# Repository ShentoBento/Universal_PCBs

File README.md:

# Universal PCBs
note: this was a draft written by AI, its got a ton of errors and is pending manual changes
**Open-source, QMK/VIA-compatible keyboard PCBs designed to fit as many cases as possible.**

Most custom keyboard cases are designed around one specific PCB. The boards in this repo work the other way around. Each one is built to drop into as many cases of its form factor as possible, by supporting a wide range of layouts and matching the connector and mounting positions that different cases expect.

---

## Boards

| Board | Form factor | Type | Status | Firmware |
|---|---|---|---|---|
| [**Uni60 Solder**](Uni60/UNI60_Solder) | 60% | Solder | Completed 50 unit GB, Sep 2026 | [Uni60/Solder](https://github.com/ShentoBento/Universal_PCBs_Firmware/tree/main/Uni60/Solder) |
| [**Uni60 Hotswap**](Uni60/UNI60_Hotswap) | 60% | Hotswap | In development | — |

Each board's folder has its own README with full specs, layout diagrams and ordering files.

---

## What "universal" means here

**Layouts.** Each board supports the common layout variations for its size. The Uni60 covers ANSI and ISO, split backspace, split left and right shift, stepped caps, and five bottom rows: 6.25u, 7u, 10u, 2.25u/1.25u/2.75u split, and 3u/1u/3u split.

**Connectors.** Enthusiast cases route the USB daughterboard cable through a channel, and that channel sits in a different place in nearly every case. A tall JST-SH connector anywhere else bottoms out on the case floor. So the Uni60 has **five daisy-chained JST-SH positions** that line up with common channel locations. Keep the one your case uses and clip or desolder the rest. There's also a **Molex Pico-EZmate** connector, which sits lower than the switch pins and fits any case.

**Outline and mounting.** The board outline is drawn to suit as many cases as possible. It includes tray-mount holes between keys, with the switch matrix routed around them.

---

## Shared specs

- **MCU:** STM32F072CBTx
- **Connectors:** JST-SH 4-pin (multiple positions) and Molex Pico-EZmate 4-pin
- **Firmware:** QMK with VIA and Vial support, in [Universal_PCBs_Firmware](https://github.com/ShentoBento/Universal_PCBs_Firmware)
- **Design tool:** KiCad 10 or newer (earlier versions won't open the files)
- **Manufacturing:** fab and assembly files generated for JLCPCB

---

## Repository layout

```
Universal_PCBs/
├── Uni60/
│   ├── UNI60_Solder/              complete: KiCad project, production files, images
│   └── UNI60_Hotswap/             in development
└── shentobento_kicad_library/     shared symbols, footprints and 3D models
```

## Using these files

1. Clone or download the **whole repo**, not just one board's folder. Every board points at the shared `shentobento_kicad_library/` with relative paths, so the projects open on any machine with no library setup.
2. Open the board's `.kicad_pro` file in KiCad 10 or newer.
3. To order boards, use the files in that board's `production/` folder (gerbers, BOM, positions). If you change the design, regenerate them with the JLCPCB Fabrication Toolkit plugin.

## Related

- [Universal_PCBs_Firmware](https://github.com/ShentoBento/Universal_PCBs_Firmware): QMK firmware for these boards
- [Velvet-Pro-Solder-PCB](https://github.com/ShentoBento/Velvet-Pro-Solder-PCB): the board whose matrix and MCU design the Uni60 builds on

## Credits and licenses

Keyboard footprints and symbols are derived from [marbastlib](https://github.com/ebastler/marbastlib) by ebastler, licensed under CERN-OHL-P v2. See `shentobento_kicad_library/LICENSE-marbastlib.txt`; modifications are logged in `shentobento_kicad_library/NOTICE.md`. Generic footprints come from the KiCad standard libraries.

---

Designed by **Andrew Shentu** ([@ShentoBento](https://github.com/ShentoBento)) · [LinkedIn](https://www.linkedin.com/in/andrewshentu)

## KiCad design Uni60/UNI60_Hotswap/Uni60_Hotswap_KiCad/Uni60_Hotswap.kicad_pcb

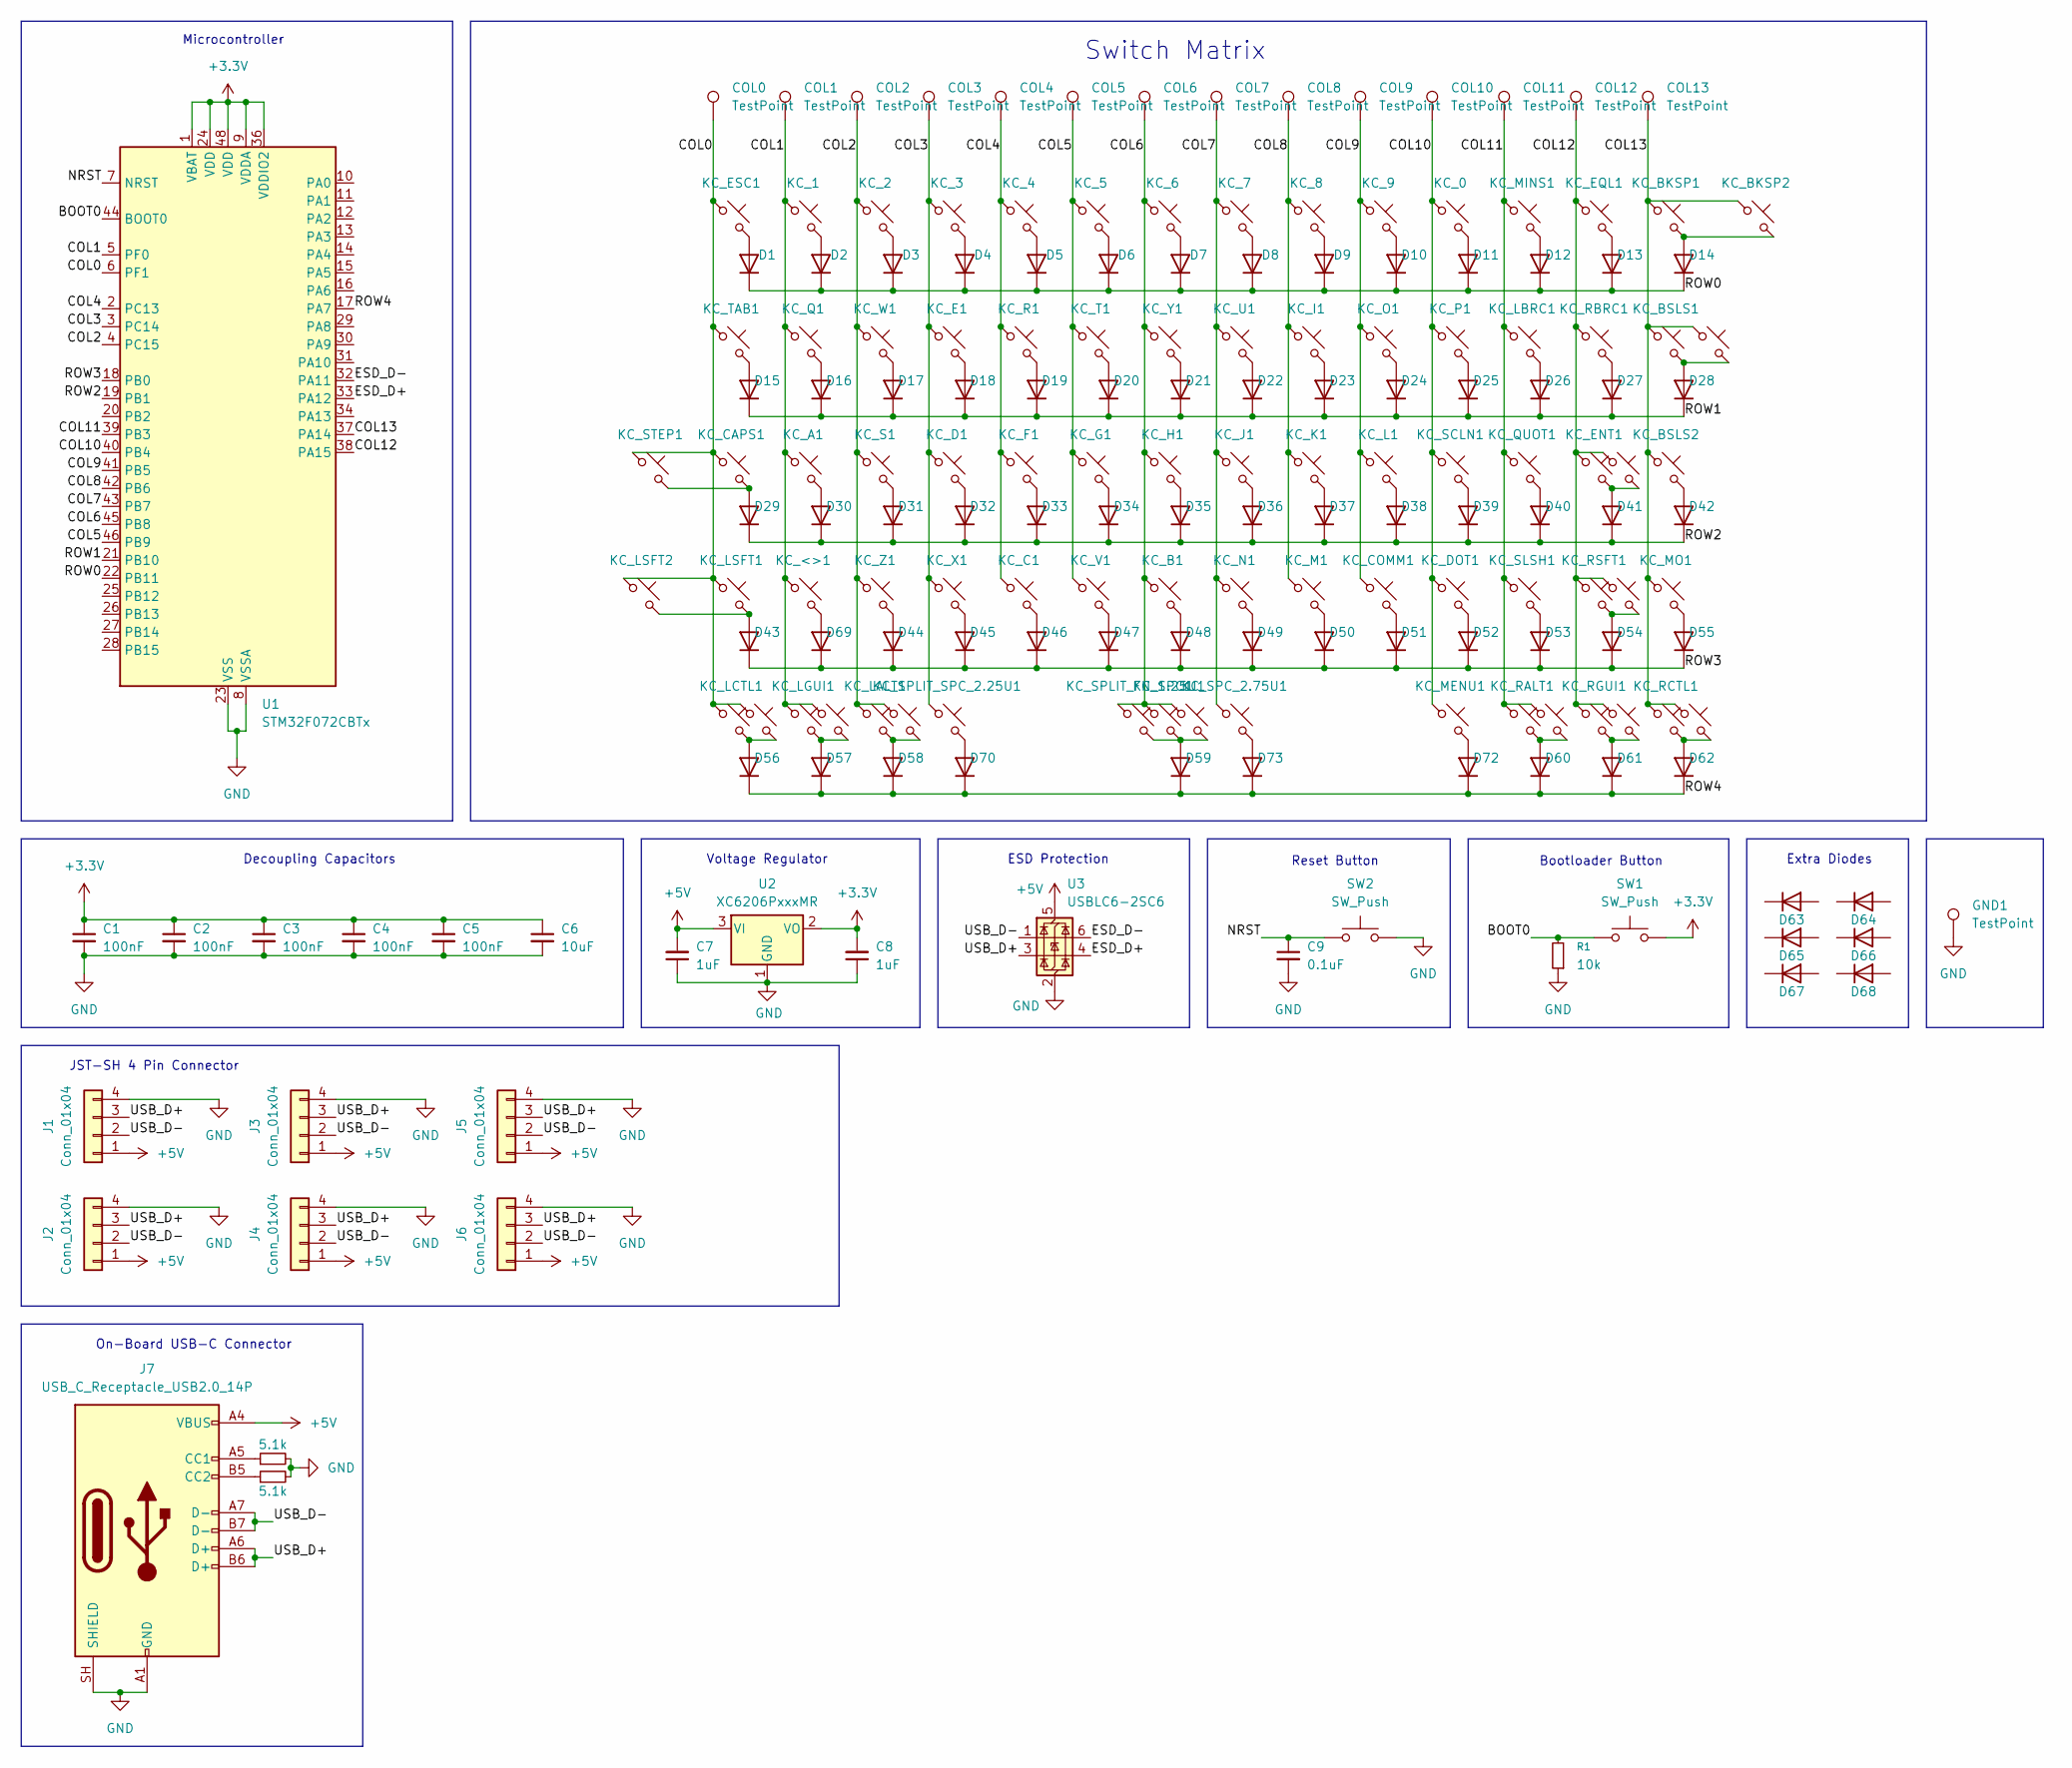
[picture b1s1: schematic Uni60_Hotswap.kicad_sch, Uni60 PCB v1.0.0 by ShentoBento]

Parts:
C1, C2, C3, C4, C5: 100nF; C_0201_0603Metric
C6: 10uF; C_0805_2012Metric
C7, C8: 1uF; C_0201_0603Metric
C9: 0.1uF; C_0201_0603Metric
COL0, COL1, COL2, COL3, COL4, COL5, COL6, COL7, COL8, COL9, COL10, COL11, COL12, COL13: TestPoint; TestPoint_Pad_1.5x1.5mm
D1, D2, D3, D4, D5, D6, D7, D8, D9, D10, D11, D12, D13, D14, D15, D16, D17, D18, D19, D20, D21, D22, D23, D24, D25, D26, D27, D28, D29, D30, D31, D32, D33, D34, D35, D36, D37, D38, D39, D40, D41, D42, D43, D44, D45, D46, D47, D48, D49, D50, D51, D52, D53, D54, D55, D56, D57, D58, D59, D60, D61, D62, D63, D64, D65, D66, D67, D68, D69, D70, D72, D73: 1N4148; D_SOD-323
GND1: TestPoint; TestPoint_Bridge_Pitch2.0mm_Drill0.7mm
J1, J2, J3, J4, J5: Conn_01x04; JST_SH_1x04
J6: Conn_01x04; Molex_Pico-EZmate_78171-0004_1x04-1MP_P1.20mm_Vertical
J7: USB_C_Receptacle_USB2.0_14P; USB_C_Receptacle_GCT_USB4105-xx-A_16P_TopMnt_Horizontal
KC_0, KC_1, KC_2, KC_3, KC_4, KC_5, KC_6, KC_7, KC_8, KC_9: MX_SW_solder; SW_MX_HS_KAILH_1u
KC_<>1: MX_SW_solder; SW_MX_HS_KAILH_1u
KC_A1: MX_SW_solder; SW_MX_HS_KAILH_1u
KC_B1: MX_SW_solder; SW_MX_HS_KAILH_1u
KC_BKSP1, KC_BKSP2: MX_SW_solder; SW_MX_HS_KAILH_1u
KC_BSLS1: MX_SW_solder; SW_MX_HS_KAILH_1.5u
KC_BSLS2: MX_SW_solder; SW_MX_HS_KAILH_1u
KC_BSLS_ISO1: MX_SW_solder; SW_MX_HS_KAILH_1u
KC_C1: MX_SW_solder; SW_MX_HS_KAILH_1u
KC_CAPS1: MX_SW_solder; SW_MX_HS_KAILH_1.75u
KC_COMM1: MX_SW_solder; SW_MX_HS_KAILH_1u
KC_D1: MX_SW_solder; SW_MX_HS_KAILH_1u
KC_DOT1: MX_SW_solder; SW_MX_HS_KAILH_1u
KC_E1: MX_SW_solder; SW_MX_HS_KAILH_1u
KC_ENT1: MX_SW_solder; SW_MX_HS_KAILH_1u
KC_ENT_ISO1: MX_SW_solder; SW_MX_HS_KAILH_1u
KC_EQL1: MX_SW_solder; SW_MX_HS_KAILH_1u
KC_ESC1: MX_SW_solder; SW_MX_HS_KAILH_1u
KC_F1: MX_SW_solder; SW_MX_HS_KAILH_1u
KC_G1: MX_SW_solder; SW_MX_HS_KAILH_1u
KC_H1: MX_SW_solder; SW_MX_HS_KAILH_1u
KC_I1: MX_SW_solder; SW_MX_HS_KAILH_1u
KC_J1: MX_SW_solder; SW_MX_HS_KAILH_1u
KC_K1: MX_SW_solder; SW_MX_HS_KAILH_1u
KC_L1: MX_SW_solder; SW_MX_HS_KAILH_1u
KC_LALT1: MX_SW_solder; SW_MX_HS_KAILH_1.5u
KC_LALT_1.25U1: MX_SW_solder; SW_MX_HS_KAILH_1.25u
KC_LBRC1: MX_SW_solder; SW_MX_HS_KAILH_1u
KC_LCTL1: MX_SW_solder; SW_MX_HS_KAILH_1.5u
KC_LCTL_1.25U1: MX_SW_solder; SW_MX_HS_KAILH_1.25u
KC_LGUI1: MX_SW_solder; SW_MX_HS_KAILH_1u
KC_LGUI_1.25U1: MX_SW_solder; SW_MX_HS_KAILH_1.25u
KC_LSFT1: MX_SW_solder; SW_MX_HS_KAILH_1u
KC_LSFT2: MX_SW_solder; SW_MX_HS_KAILH_1.25u
KC_M1: MX_SW_solder; SW_MX_HS_KAILH_1u
KC_MENU1: MX_SW_solder; SW_MX_HS_KAILH_1.25u
KC_MINS1: MX_SW_solder; SW_MX_HS_KAILH_1u
KC_MO1: MX_SW_solder; SW_MX_HS_KAILH_1u
KC_N1: MX_SW_solder; SW_MX_HS_KAILH_1u
KC_O1: MX_SW_solder; SW_MX_HS_KAILH_1u
KC_P1: MX_SW_solder; SW_MX_HS_KAILH_1u
KC_Q1: MX_SW_solder; SW_MX_HS_KAILH_1u
KC_QUOT1: MX_SW_solder; SW_MX_HS_KAILH_1u
KC_R1: MX_SW_solder; SW_MX_HS_KAILH_1u
KC_RALT1: MX_SW_solder; SW_MX_HS_KAILH_1.5u
KC_RALT_1.25U1: MX_SW_solder; SW_MX_HS_KAILH_1.25u
KC_RBRC1: MX_SW_solder; SW_MX_HS_KAILH_1u
KC_RCTL1: MX_SW_solder; SW_MX_HS_KAILH_1.5u
KC_RCTL_1.25U1: MX_SW_solder; SW_MX_HS_KAILH_1.25u
KC_RGUI1: MX_SW_solder; SW_MX_HS_KAILH_1u
KC_RGUI_1.25U1: MX_SW_solder; SW_MX_HS_KAILH_1.25u
KC_RSFT1: MX_SW_solder; SW_MX_HS_KAILH_1u
KC_RSFT_2.75u1: MX_SW_solder; SW_MX_HS_KAILH_1u
KC_S1: MX_SW_solder; SW_MX_HS_KAILH_1u
KC_SCLN1: MX_SW_solder; SW_MX_HS_KAILH_1u
KC_SLSH1: MX_SW_solder; SW_MX_HS_KAILH_1u
KC_SPC1: MX_SW_solder; SW_MX_HS_KAILH_1u
KC_SPC_2.75U1, KC_SPC_6.25U1: MX_SW_solder; SW_MX_HS_KAILH_1u
KC_SPLIT_FN_1.25U1: MX_SW_solder; SW_MX_HS_KAILH_1.25u
KC_SPLIT_SPC_2.25U1: MX_SW_solder; SW_MX_HS_KAILH_1u
KC_STEP1: MX_SW_solder; SW_MX_HS_KAILH_1.75u_STEPPED_1.25
KC_T1: MX_SW_solder; SW_MX_HS_KAILH_1u
KC_TAB1: MX_SW_solder; SW_MX_HS_KAILH_1.5u
KC_U1: MX_SW_solder; SW_MX_HS_KAILH_1u
KC_V1: MX_SW_solder; SW_MX_HS_KAILH_1u
KC_W1: MX_SW_solder; SW_MX_HS_KAILH_1u
KC_X1: MX_SW_solder; SW_MX_HS_KAILH_1u
KC_Y1: MX_SW_solder; SW_MX_HS_KAILH_1u
KC_Z1: MX_SW_solder; SW_MX_HS_KAILH_1u
R1: 10k; R_0201_0603Metric
R2, R3: 5.1k; R_0201_0603Metric
SW1, SW2: SW_Push; SW_Push_Reset_Bootloader
U1: STM32F072CBTx; MCU_STM32F072CBTx
U2: XC6206PxxxMR; SOT-23-3
U3: USBLC6-2SC6; SOT-23-6

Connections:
+3.3V: C1.1, C2.1, C3.1, C4.1, C5.1, C6.1, C8.2, SW1.2, U1.1 (VBAT), U1.9 (VDDA), U1.24 (VDD), U1.36 (VDDIO2), U1.48 (VDD), U2.2 (VO)
+5V: C7.2, J1.1, J2.1, J3.1, J4.1, J5.1, J6.1, J7.A4 (VBUS), J7.A9 (VBUS), J7.B4 (VBUS), J7.B9 (VBUS), U2.3 (VI), U3.5 (VBUS)
/BOOT0: R1.2, SW1.1, U1.44 (BOOT0)
/COL0: COL0.1 (1_1), KC_CAPS1.1, KC_ESC1.1, KC_LCTL1.1, KC_LCTL_1.25U1.1, KC_LSFT1.1, KC_LSFT2.1, KC_STEP1.1, KC_TAB1.1, U1.6 (PF1)
/COL1: COL1.1 (1_1), KC_1.1, KC_<>1.1, KC_A1.1, KC_LGUI1.1, KC_LGUI_1.25U1.1, KC_Q1.1, U1.5 (PF0)
/COL2: COL2.1 (1_1), KC_2.1, KC_LALT1.1, KC_LALT_1.25U1.1, KC_S1.1, KC_W1.1, KC_Z1.1, U1.4 (PC15)
/COL3: COL3.1 (1_1), KC_3.1, KC_D1.1, KC_E1.1, KC_SPLIT_SPC_2.25U1.1, KC_X1.1, U1.3 (PC14)
/COL4: COL4.1 (1_1), KC_4.1, KC_C1.1, KC_F1.1, KC_R1.1, U1.2 (PC13)
/COL5: COL5.1 (1_1), KC_5.1, KC_G1.1, KC_T1.1, KC_V1.1, U1.46 (PB9)
/COL6: COL6.1 (1_1), KC_6.1, KC_B1.1, KC_H1.1, KC_SPC1.1, KC_SPC_6.25U1.1, KC_SPLIT_FN_1.25U1.1, KC_Y1.1, U1.45 (PB8)
/COL7: COL7.1 (1_1), KC_7.1, KC_J1.1, KC_N1.1, KC_SPC_2.75U1.1, KC_U1.1, U1.43 (PB7)
/COL8: COL8.1 (1_1), KC_8.1, KC_I1.1, KC_K1.1, KC_M1.1, U1.42 (PB6)
/COL9: COL9.1 (1_1), KC_9.1, KC_COMM1.1, KC_L1.1, KC_O1.1, U1.41 (PB5)
/COL10: COL10.1 (1_1), KC_0.1, KC_DOT1.1, KC_MENU1.1, KC_P1.1, KC_SCLN1.1, U1.40 (PB4)
/COL11: COL11.1 (1_1), KC_LBRC1.1, KC_MINS1.1, KC_QUOT1.1, KC_RALT1.1, KC_RALT_1.25U1.1, KC_SLSH1.1, U1.39 (PB3)
/COL12: COL12.1 (1_1), KC_ENT1.1, KC_ENT_ISO1.1, KC_EQL1.1, KC_RBRC1.1, KC_RGUI1.1, KC_RGUI_1.25U1.1, KC_RSFT1.1, KC_RSFT_2.75u1.1, U1.38 (PA15)
/COL13: COL13.1 (1_1), KC_BKSP1.1, KC_BKSP2.1, KC_BSLS1.1, KC_BSLS2.1, KC_BSLS_ISO1.1, KC_MO1.1, KC_RCTL1.1, KC_RCTL_1.25U1.1, U1.37 (PA14)
/ESD_D+: U1.33 (PA12), U3.4 (I/O2)
/ESD_D-: U1.32 (PA11), U3.6 (I/O1)
/NRST: C9.1, SW2.1, U1.7 (NRST)
/ROW0: D1.1 (K), D2.1 (K), D3.1 (K), D4.1 (K), D5.1 (K), D6.1 (K), D7.1 (K), D8.1 (K), D9.1 (K), D10.1 (K), D11.1 (K), D12.1 (K), D13.1 (K), D14.1 (K), U1.22 (PB11)
/ROW1: D15.1 (K), D16.1 (K), D17.1 (K), D18.1 (K), D19.1 (K), D20.1 (K), D21.1 (K), D22.1 (K), D23.1 (K), D24.1 (K), D25.1 (K), D26.1 (K), D27.1 (K), D28.1 (K), U1.21 (PB10)
/ROW2: D29.1 (K), D30.1 (K), D31.1 (K), D32.1 (K), D33.1 (K), D34.1 (K), D35.1 (K), D36.1 (K), D37.1 (K), D38.1 (K), D39.1 (K), D40.1 (K), D41.1 (K), D42.1 (K), U1.19 (PB1)
/ROW3: D43.1 (K), D44.1 (K), D45.1 (K), D46.1 (K), D47.1 (K), D48.1 (K), D49.1 (K), D50.1 (K), D51.1 (K), D52.1 (K), D53.1 (K), D54.1 (K), D55.1 (K), D69.1 (K), U1.18 (PB0)
/ROW4: D56.1 (K), D57.1 (K), D58.1 (K), D59.1 (K), D60.1 (K), D61.1 (K), D62.1 (K), D70.1 (K), D72.1 (K), D73.1 (K), U1.17 (PA7)
/USB_D+: J1.3, J2.3, J3.3, J4.3, J5.3, J6.3, J7.A6 (D+), J7.B6 (D+), U3.3 (I/O2)
/USB_D-: J1.2, J2.2, J3.2, J4.2, J5.2, J6.2, J7.A7 (D-), J7.B7 (D-), U3.1 (I/O1)
GND: C1.2, C2.2, C3.2, C4.2, C5.2, C6.2, C7.1, C8.1, C9.2, GND1.1 (1_1), J1.4, J2.4, J3.4, J4.4, J5.4, J6.4, J7.A1 (GND), J7.A12 (GND), J7.B1 (GND), J7.B12 (GND), J7.SH (SHIELD), R1.1, R2.2, R3.2, SW2.2, U1.8 (VSSA), U1.23 (VSS), U1.35 (VSS), U1.47 (VSS), U2.1 (GND), U3.2 (GND)
unnamed: D1.2 (A), KC_ESC1.2
unnamed: D2.2 (A), KC_1.2
unnamed: D3.2 (A), KC_2.2
unnamed: D4.2 (A), KC_3.2
unnamed: D5.2 (A), KC_4.2
unnamed: D6.2 (A), KC_5.2
unnamed: D7.2 (A), KC_6.2
unnamed: D8.2 (A), KC_7.2
unnamed: D9.2 (A), KC_8.2
unnamed: D10.2 (A), KC_9.2
unnamed: D11.2 (A), KC_0.2
unnamed: D12.2 (A), KC_MINS1.2
unnamed: D13.2 (A), KC_EQL1.2
unnamed: D14.2 (A), KC_BKSP1.2, KC_BKSP2.2
unnamed: D15.2 (A), KC_TAB1.2
unnamed: D16.2 (A), KC_Q1.2
unnamed: D17.2 (A), KC_W1.2
unnamed: D18.2 (A), KC_E1.2
unnamed: D19.2 (A), KC_R1.2
unnamed: D20.2 (A), KC_T1.2
unnamed: D21.2 (A), KC_Y1.2
unnamed: D22.2 (A), KC_U1.2
unnamed: D23.2 (A), KC_I1.2
unnamed: D24.2 (A), KC_O1.2
unnamed: D25.2 (A), KC_P1.2
unnamed: D26.2 (A), KC_LBRC1.2
unnamed: D27.2 (A), KC_RBRC1.2
unnamed: D28.2 (A), KC_BSLS1.2, KC_BSLS_ISO1.2
unnamed: D29.2 (A), KC_CAPS1.2, KC_STEP1.2
unnamed: D30.2 (A), KC_A1.2
unnamed: D31.2 (A), KC_S1.2
unnamed: D32.2 (A), KC_D1.2
unnamed: D33.2 (A), KC_F1.2
unnamed: D34.2 (A), KC_G1.2
unnamed: D35.2 (A), KC_H1.2
unnamed: D36.2 (A), KC_J1.2
unnamed: D37.2 (A), KC_K1.2
unnamed: D38.2 (A), KC_L1.2
unnamed: D39.2 (A), KC_SCLN1.2
unnamed: D40.2 (A), KC_QUOT1.2
unnamed: D41.2 (A), KC_ENT1.2, KC_ENT_ISO1.2
unnamed: D42.2 (A), KC_BSLS2.2
unnamed: D43.2 (A), KC_LSFT1.2, KC_LSFT2.2
unnamed: D44.2 (A), KC_Z1.2
unnamed: D45.2 (A), KC_X1.2
unnamed: D46.2 (A), KC_C1.2
unnamed: D47.2 (A), KC_V1.2
unnamed: D48.2 (A), KC_B1.2
unnamed: D49.2 (A), KC_N1.2
unnamed: D50.2 (A), KC_M1.2
unnamed: D51.2 (A), KC_COMM1.2
unnamed: D52.2 (A), KC_DOT1.2
unnamed: D53.2 (A), KC_SLSH1.2
unnamed: D54.2 (A), KC_RSFT1.2, KC_RSFT_2.75u1.2
unnamed: D55.2 (A), KC_MO1.2
unnamed: D56.2 (A), KC_LCTL1.2, KC_LCTL_1.25U1.2
unnamed: D57.2 (A), KC_LGUI1.2, KC_LGUI_1.25U1.2
unnamed: D58.2 (A), KC_LALT1.2, KC_LALT_1.25U1.2
unnamed: D59.2 (A), KC_SPC1.2, KC_SPC_6.25U1.2, KC_SPLIT_FN_1.25U1.2
unnamed: D60.2 (A), KC_RALT1.2, KC_RALT_1.25U1.2
unnamed: D61.2 (A), KC_RGUI1.2, KC_RGUI_1.25U1.2
unnamed: D62.2 (A), KC_RCTL1.2, KC_RCTL_1.25U1.2
unnamed: D69.2 (A), KC_<>1.2
unnamed: D70.2 (A), KC_SPLIT_SPC_2.25U1.2
unnamed: D72.2 (A), KC_MENU1.2
unnamed: D73.2 (A), KC_SPC_2.75U1.2
unnamed: J7.A5 (CC1), R2.1
unnamed: J7.B5 (CC2), R3.1

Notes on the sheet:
Reset Button
Microcontroller
Voltage Regulator
Extra Diodes
JST-SH 4 Pin Connector
Bootloader Button
On-Board USB-C Connector
ESD Protection
Decoupling Capacitors
Switch Matrix

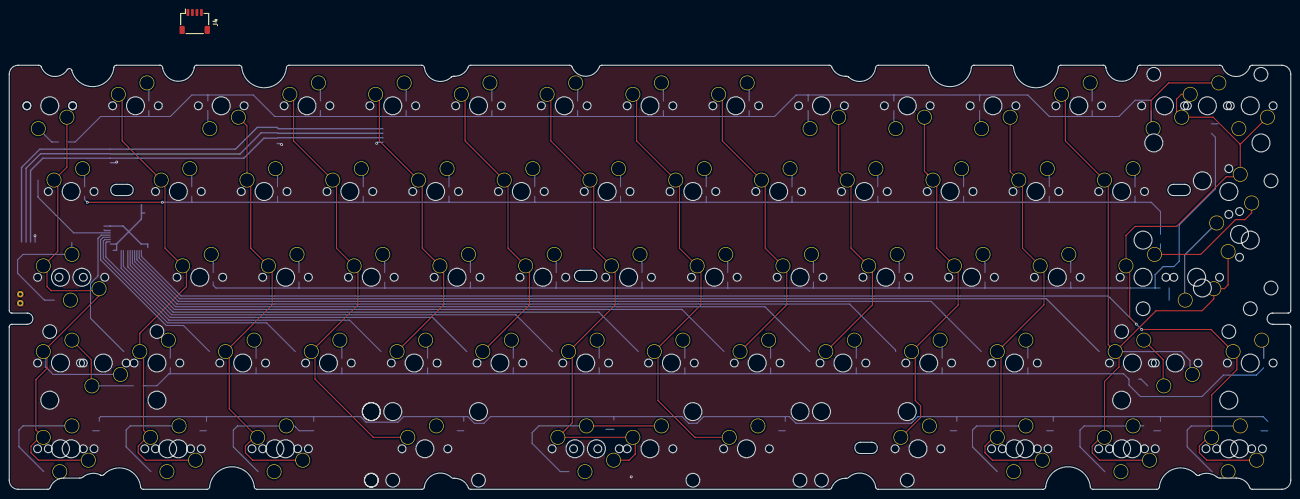
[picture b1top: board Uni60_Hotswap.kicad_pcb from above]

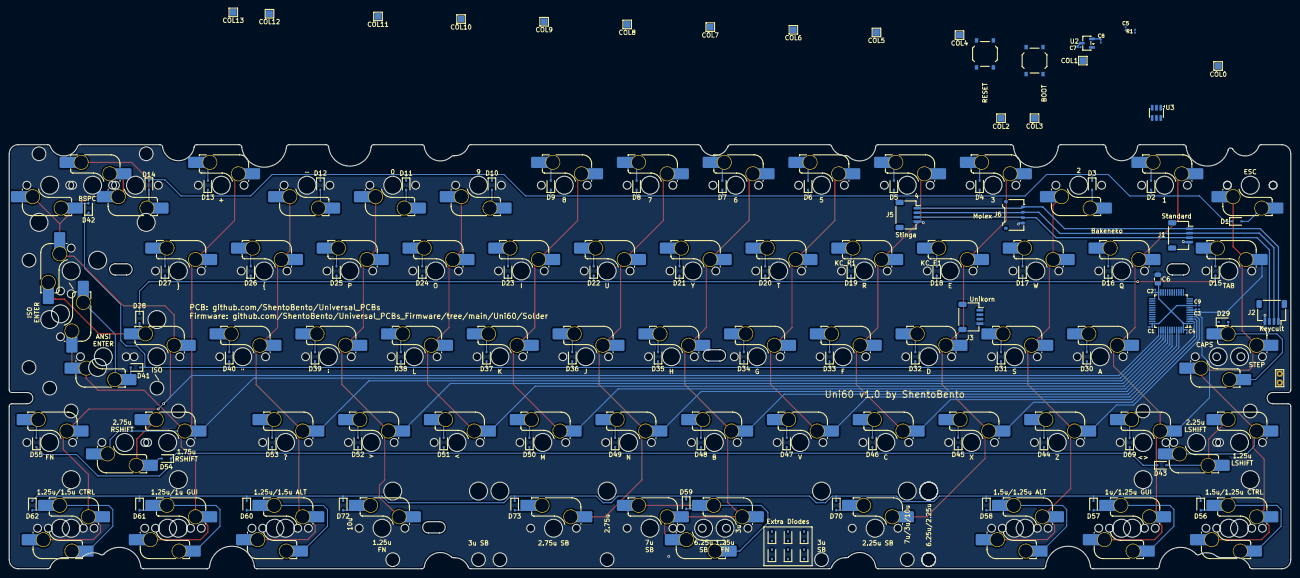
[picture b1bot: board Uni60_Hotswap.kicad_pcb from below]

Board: 2 copper layers, 284.7 x 94.2 mm, 188 parts (187 on the bottom side), 94 nets.
